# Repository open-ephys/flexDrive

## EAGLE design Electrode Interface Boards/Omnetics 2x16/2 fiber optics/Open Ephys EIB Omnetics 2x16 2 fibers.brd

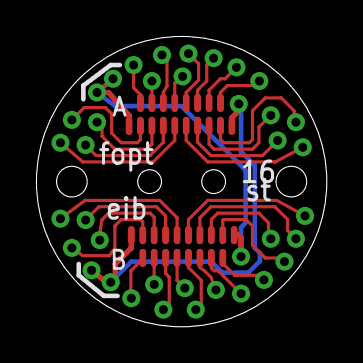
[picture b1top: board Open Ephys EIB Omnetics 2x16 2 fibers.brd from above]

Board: 2 copper layers, 16.1 x 16.1 mm, 40 parts (0 on the bottom side), 34 nets.

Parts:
U$1, U$2: OMNETICS_FE18
U$3, U$4, U$5, U$6, U$7, U$8, U$9, U$10, U$11, U$12, U$13, U$14, U$15, U$16, U$17, U$18, U$19, U$20, U$21, U$22, U$23, U$24, U$25, U$26, U$27, U$28, U$29, U$30, U$31, U$32, U$33, U$34, U$35, U$36, U$37, U$38, U$39, U$40: GOLDPINLARGE; LARGEGOLDPIN

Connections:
unnamed: U$2.P$15, U$28.P1
unnamed: U$2.P$14, U$29.P1
unnamed: U$1.P$8, U$3.P1
unnamed: U$1.P$7, U$5.P1
unnamed: U$1.P$6, U$4.P1
unnamed: U$1.P$5, U$6.P1
unnamed: U$1.P$4, U$7.P1
unnamed: U$1.P$3, U$8.P1
unnamed: U$1.P$2, U$9.P1
unnamed: U$1.P$1, U$10.P1
unnamed: U$1.P$16, U$18.P1
unnamed: U$1.P$15, U$17.P1
unnamed: U$1.P$14, U$16.P1
unnamed: U$1.P$13, U$15.P1
unnamed: U$1.P$12, U$14.P1
unnamed: U$1.P$11, U$13.P1
unnamed: U$1.P$10, U$12.P1
unnamed: U$1.P$9, U$11.P1
unnamed: U$2.P$1, U$26.P1
unnamed: U$2.P$2, U$25.P1
unnamed: U$2.P$3, U$24.P1
unnamed: U$2.P$4, U$23.P1
unnamed: U$2.P$5, U$22.P1
unnamed: U$2.P$6, U$21.P1
unnamed: U$2.P$7, U$20.P1
unnamed: U$2.P$8, U$19.P1
unnamed: U$2.P$9, U$36.P1
unnamed: U$2.P$10, U$35.P1
unnamed: U$2.P$11, U$34.P1
unnamed: U$2.P$12, U$33.P1
unnamed: U$2.P$13, U$32.P1
unnamed: U$2.P$16, U$27.P1
unnamed: U$1.P$17, U$2.P$17, U$31.P1, U$39.P1, U$40.P1
REF1: U$1.P$18, U$2.P$18, U$30.P1, U$37.P1, U$38.P1
